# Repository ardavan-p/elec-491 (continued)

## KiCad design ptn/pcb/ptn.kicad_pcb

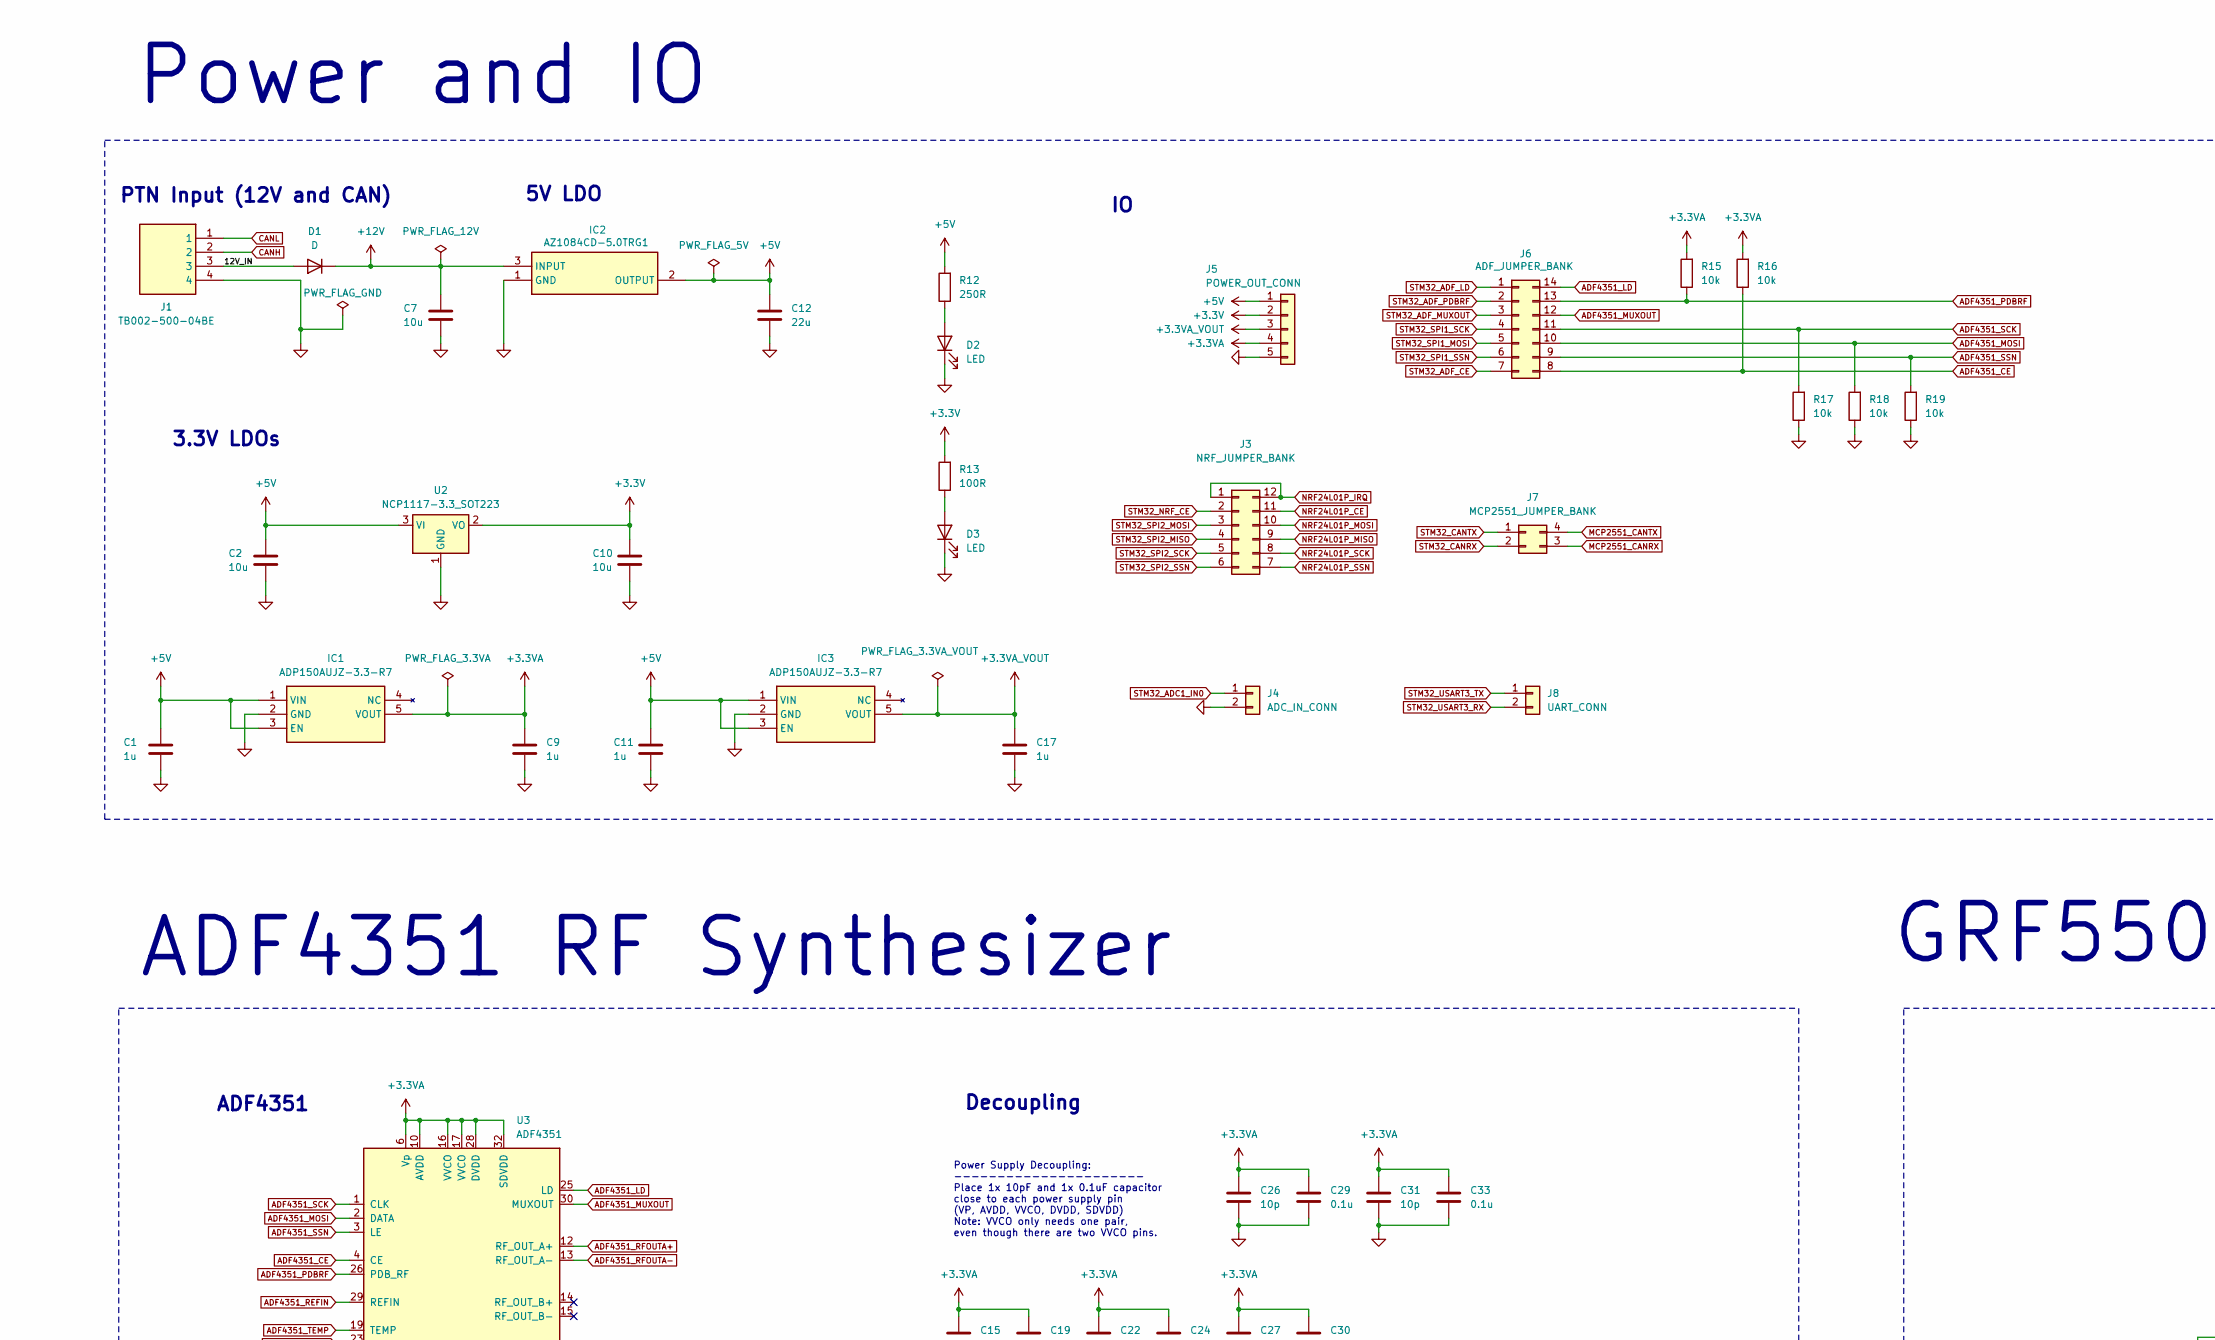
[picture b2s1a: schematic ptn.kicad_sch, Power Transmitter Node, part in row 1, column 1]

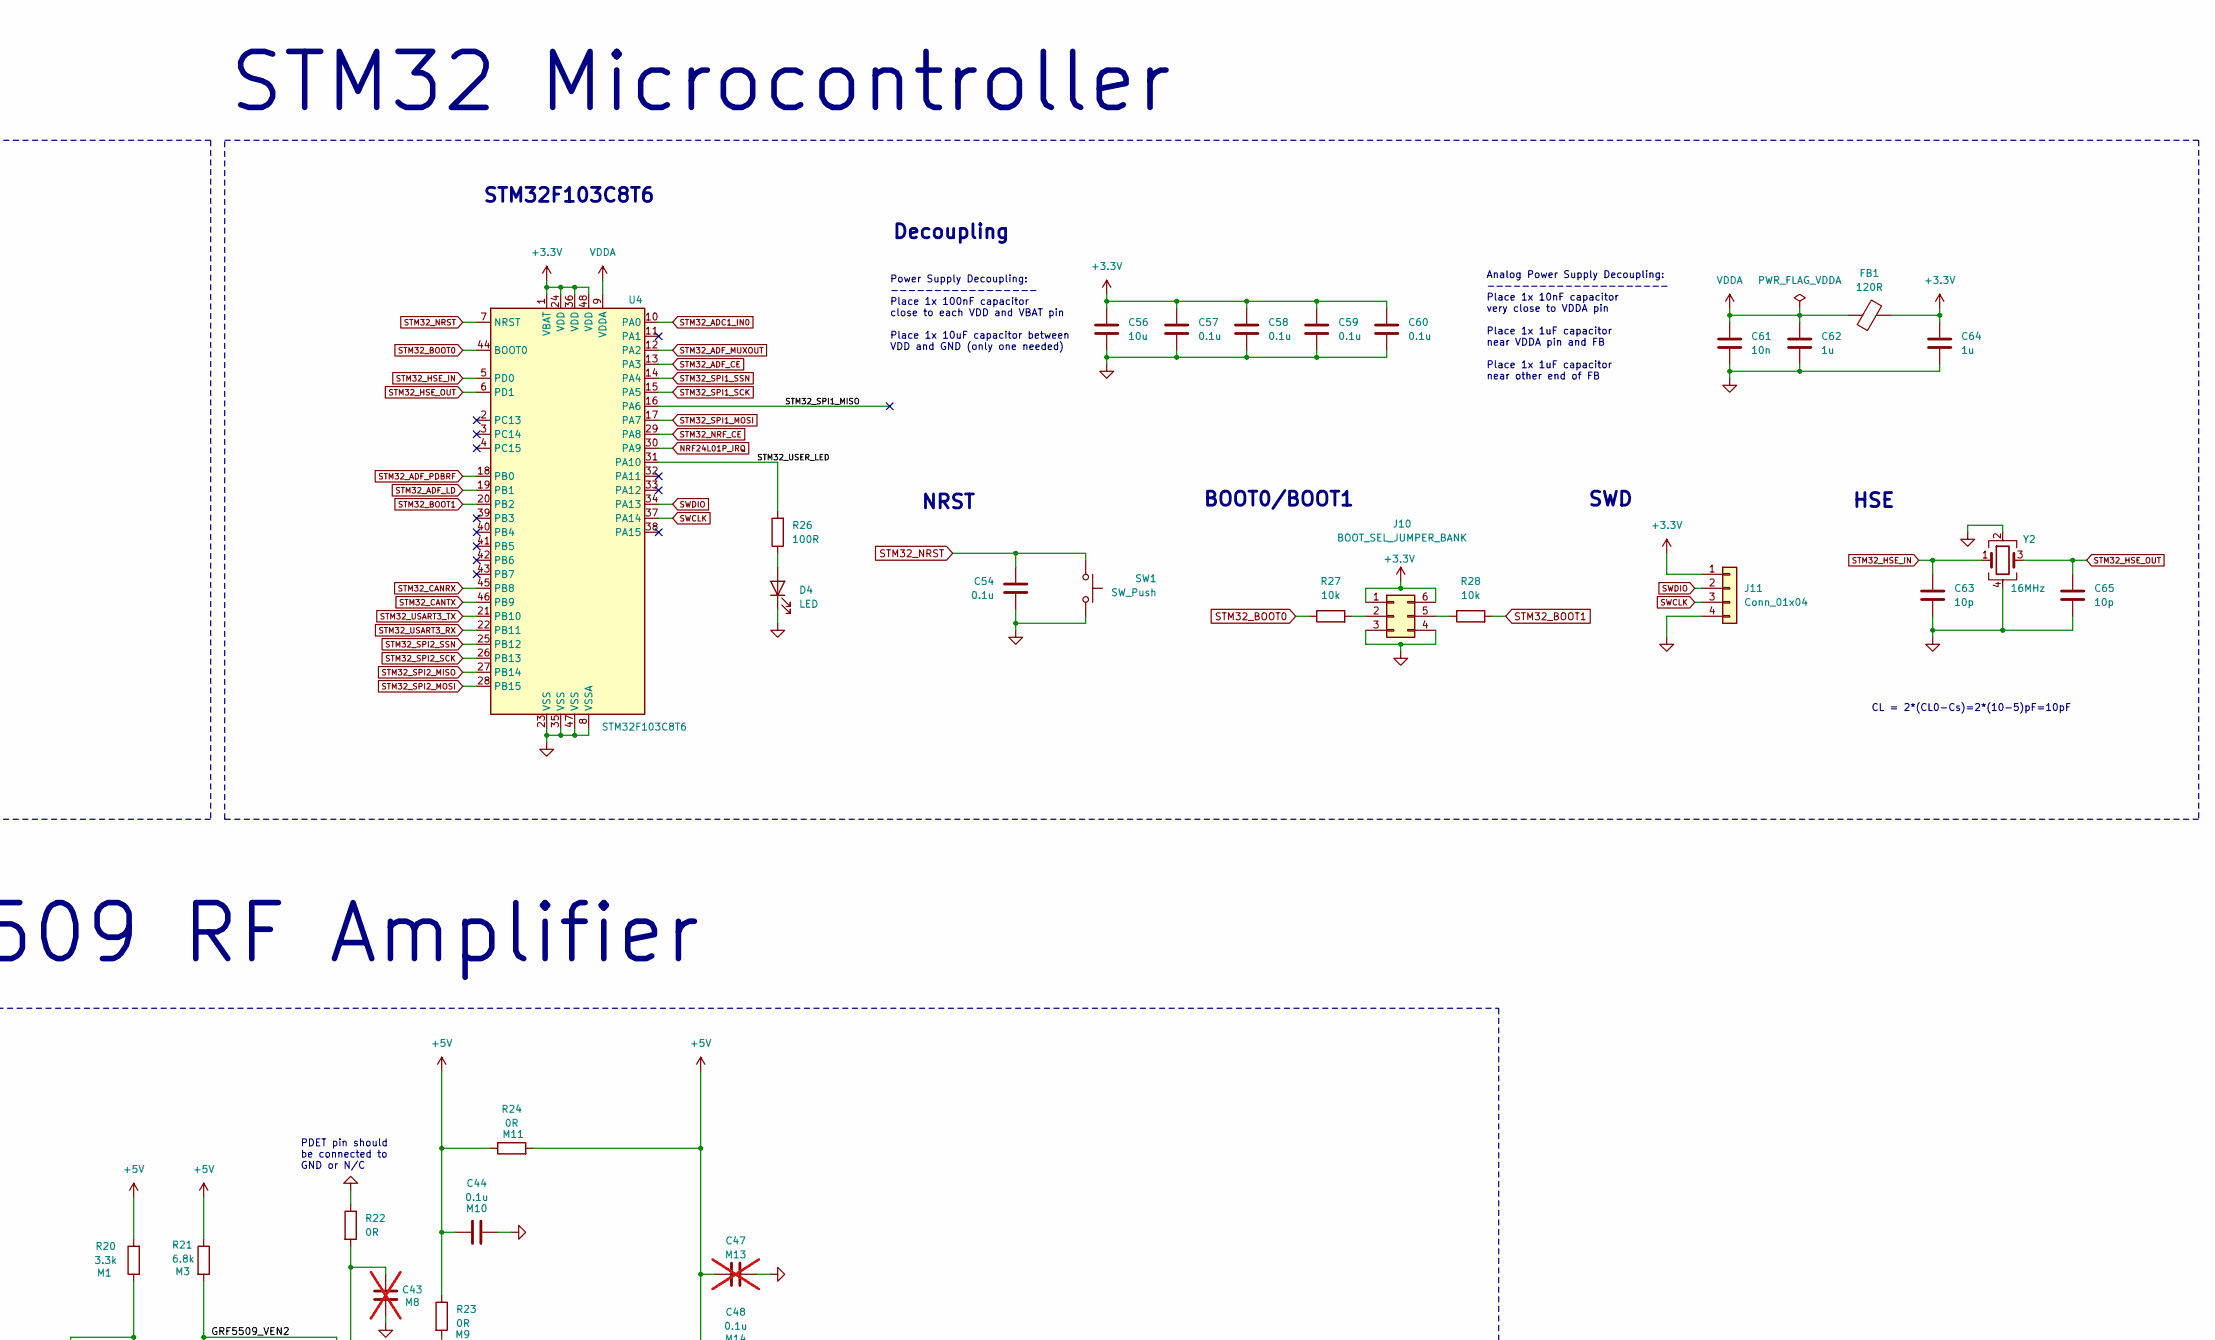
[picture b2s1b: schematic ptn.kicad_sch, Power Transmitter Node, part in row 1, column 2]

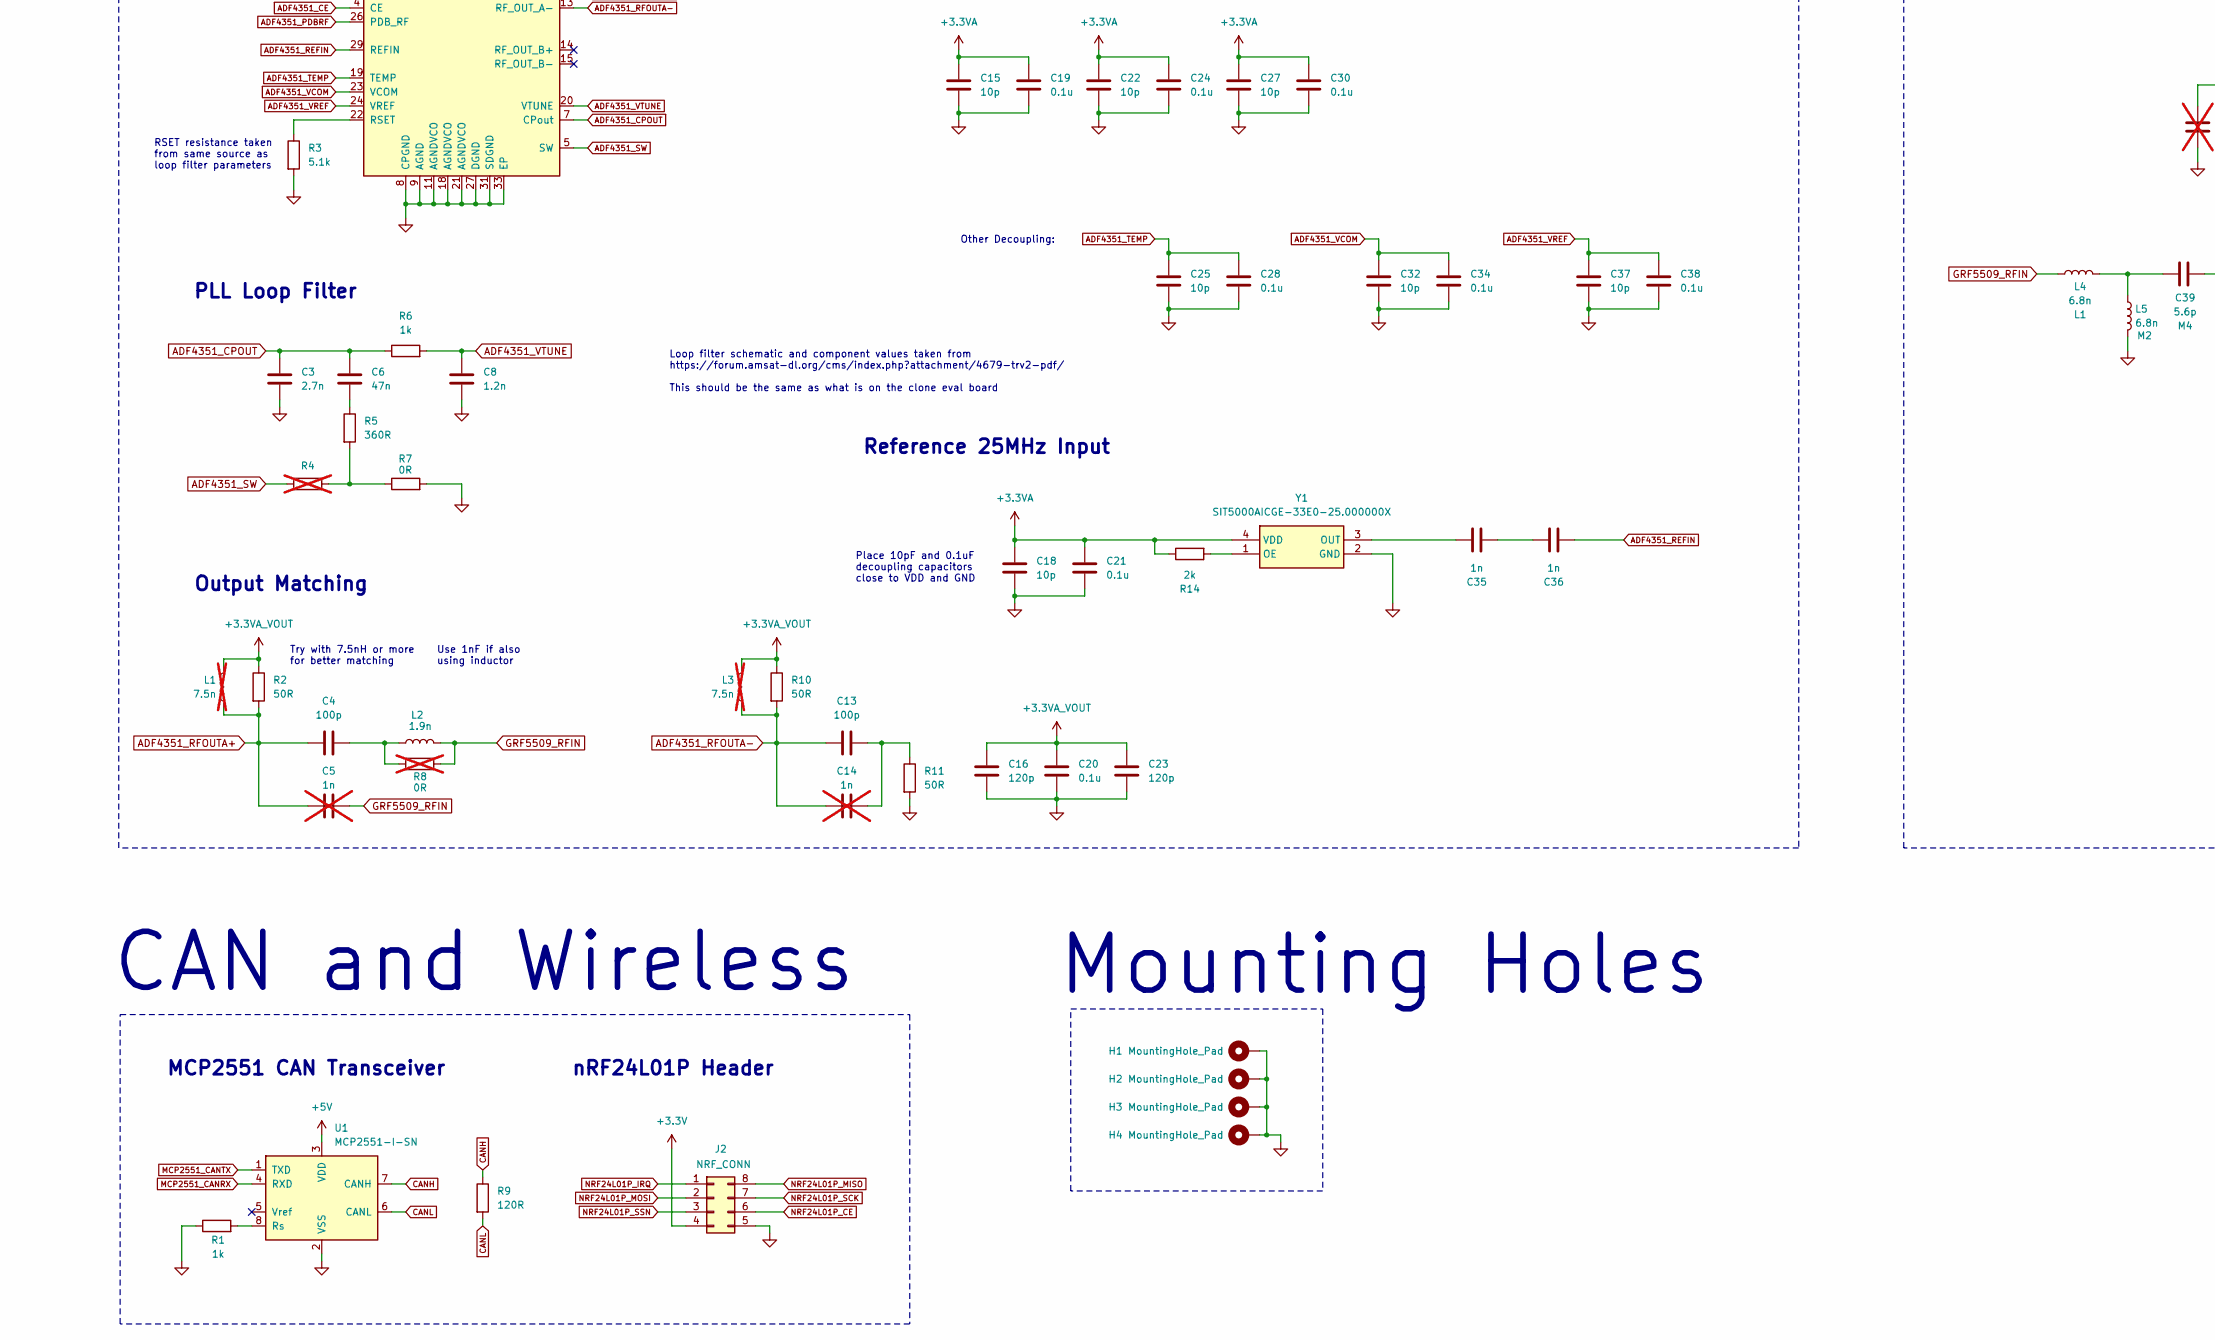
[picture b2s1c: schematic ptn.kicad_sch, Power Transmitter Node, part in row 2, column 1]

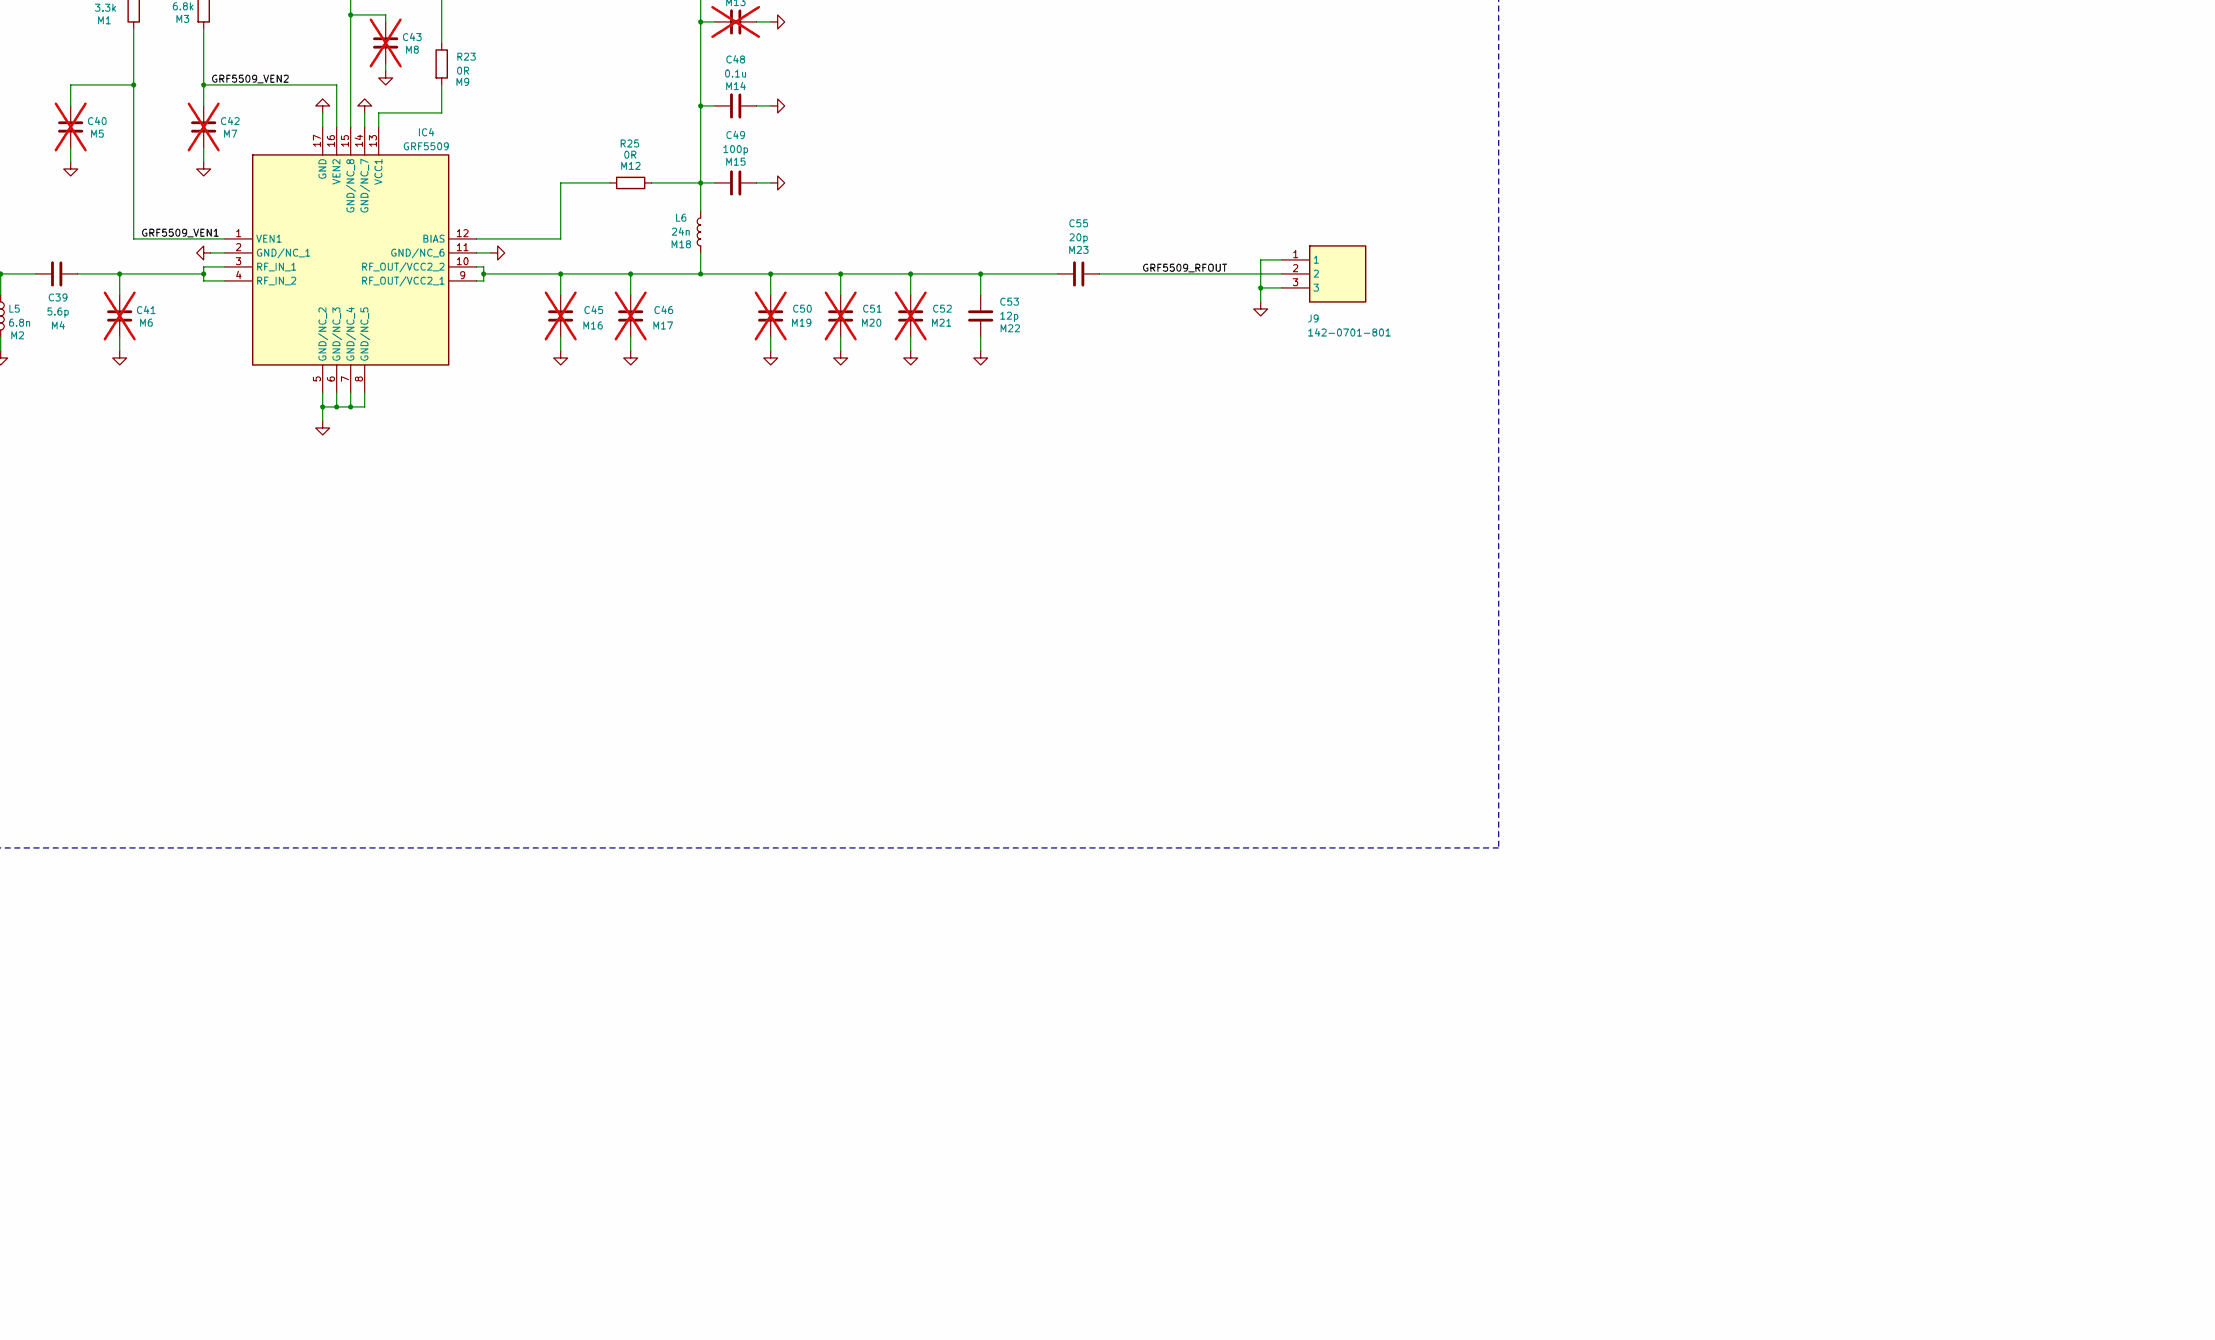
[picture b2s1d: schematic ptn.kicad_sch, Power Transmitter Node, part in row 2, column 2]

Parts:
C1, C9, C11, C17, C62, C64: 1u; C_0603_1608Metric; Manufacturer_Part_Number C0603C105K3PACTU; Mouser Part Number 80-C0603C105K3P
C2, C7, C10, C56: 10u; C_0805_2012Metric; Manufacturer_Part_Number GRM21BR61E106KA73K; Mouser Part Number 81-GRM21BR61E106KA3K
C3: 2.7n; C_0603_1608Metric; Manufacturer_Part_Number 06031C272JAT2A; Mouser Part Number 581-06031C272JAT2A
C4, C13, C49: 100p; C_0402_1005Metric; Manufacturer_Part_Number GRM1555C1H101FA01D; Mouser Part Number 81-GRM1555C1H101FA1D
C5, C14: 1n; C_0402_1005Metric; Manufacturer_Part_Number GRM1555C1H102FA01D; Mouser Part Number 81-GRM1555C1H102FA1D; not fitted
C6: 47n; C_0603_1608Metric; Manufacturer_Part_Number C0603C473J3RACTU; Mouser Part Number 80-C0603C473J3R
C8: 1.2n; C_0603_1608Metric; Manufacturer_Part_Number C0603C122J5RACTU; Mouser Part Number 80-C0603C122J5R
C12: 22u; C_0805_2012Metric; Manufacturer_Part_Number GRM21BR61E226ME44K; Mouser Part Number 81-GRM21BR61E226ME4K
C15, C18, C22, C25, C26, C27, C31, C32, C37, C63, C65: 10p; C_0402_1005Metric; Manufacturer_Part_Number GCM1555C1H100JA16J; Mouser Part Number 81-GCM1555C1H100JA6J
C16, C23: 120p; C_0402_1005Metric; Manufacturer_Part_Number GRM1555C1H121FA01D; Mouser Part Number 81-GRM1555C1H121FA1D
C19, C20, C21, C24, C28, C29, C30, C33, C34, C38, C44, C48, C54, C57, C58, C59, C60: 0.1u; C_0402_1005Metric; Manufacturer_Part_Number GRM155R71C104JA88J; Mouser Part Number 81-GRM155R71C104JA8J
C35, C36: 1n; C_0603_1608Metric; Manufacturer_Part_Number 06035A102JAT2A; Mouser Part Number 581-06035A102J
C39: 5.6p; C_0402_1005Metric; Manufacturer_Part_Number GJM1555C1H5R6WB01D; Mouser Part Number 81-GJM1555C1H5R6WB1D
C40, C41, C42, C43, C45, C46, C47, C50, C51, C52: C_0402_1005Metric; not fitted
C53: 12p; C_0402_1005Metric; Manufacturer_Part_Number GJM1555C1H120FB01D; Mouser Part Number 81-GJM1555C1H120FB1D
C55: 20p; C_0402_1005Metric; Manufacturer_Part_Number GJM1555C1H200FB01D; Mouser Part Number 81-GJM1555C1H200FB1D
C61: 10n; C_0402_1005Metric; Manufacturer_Part_Number C0402C103J8RACTU; Mouser Part Number 80-C0402C103J8RACTU
D1: D; RF302LAM2STR_DIODE; Manufacturer_Part_Number RF302LAM2STR; Mouser Part Number 755-RF302LAM2STR
D2, D3, D4: LED; LED_0603_1608Metric; Manufacturer_Part_Number 150060VS55040; Mouser Part Number 710-150060VS55040
FB1: 120R; L_0603_1608Metric; Manufacturer_Part_Number MFBM1V1608-121-R; Mouser Part Number 704-MFBM1V1608-121-R
H1, H2, H3, H4: MountingHole_Pad; MountingHole_4.3mm_M4_Pad
IC1, IC3: ADP150AUJZ-3.3-R7; SOT95P280X100-5N; Mouser Part Number 584-ADP150AUJZ-3.3R7
IC2: AZ1084CD-5.0TRG1; AZ1084CD50TRG1_LDO_5V; Mouser Part Number 621-AZ1084CD-5.0TRG1
IC4: GRF5509; QFN50P300X300X85-17N; Mouser Part Number 459-GRF5509
J1: TB002-500-04BE; TB00250004BE_SCREW_TERMINAL; Mouser Part Number 490-TB002-500-04BE
J2: NRF_CONN; PinSocket_2x04_P2.54mm_Vertical
J3: NRF_JUMPER_BANK; PinHeader_2x06_P2.54mm_Vertical
J4: ADC_IN_CONN; PinHeader_1x02_P2.54mm_Vertical
J5: POWER_OUT_CONN; PinHeader_1x05_P2.54mm_Vertical
J6: ADF_JUMPER_BANK; PinHeader_2x07_P2.54mm_Vertical
J7: MCP2551_JUMPER_BANK; PinHeader_2x02_P2.54mm_Vertical
J8: UART_CONN; PinHeader_1x02_P2.54mm_Vertical
J9: 142-0701-801; 142-0701-851; Mouser Part Number 530-142-0701-801
J10: BOOT_SEL_JUMPER_BANK; PinHeader_2x03_P2.54mm_Vertical
J11: Conn_01x04; PinHeader_1x04_P2.54mm_Vertical
L1, L3: 7.5n; L_0402_1005Metric; Manufacturer_Part_Number LQW15AN7N5G80D; Mouser Part Number 81-LQW15AN7N5G80D; not fitted
L2: 1.9n; L_0402_1005Metric; Manufacturer_Part_Number LQG15WZ1N9C02D; Mouser Part Number 81-LQG15WZ1N9C02D
L4, L5: 6.8n; L_0402_1005Metric; Manufacturer_Part_Number LQG15WH6N8G02D; Mouser Part Number 81-LQG15WH6N8G02D
L6: 24n; L_0603_1608Metric; Manufacturer_Part_Number LQW18AN24NG80D; Mouser Part Number 81-LQW18AN24NG80D
R1, R6: 1k; R_0603_1608Metric; Manufacturer_Part_Number RC0603FR-101KL; Mouser Part Number 603-RC0603FR-101KL
R2, R10, R11: 50R; R_0402_1005Metric; Manufacturer_Part_Number RC0402JR-0750RL; Mouser Part Number 603-RC0402JR-0750RL
R3: 5.1k; R_0603_1608Metric; Manufacturer_Part_Number CRCW06035K10FKEC; Mouser Part Number 71-CRCW06035K10FKEC
R4: R_0603_1608Metric; not fitted
R5: 360R; R_0603_1608Metric; Manufacturer_Part_Number RT0603DRE07360RL; Mouser Part Number 603-RT0603DRE07360RL
R7: 0R; R_0603_1608Metric; Manufacturer_Part_Number RCS06030000Z0EA; Mouser Part Number 71-RCS06030000Z0EA
R8: 0R; R_0402_1005Metric; Manufacturer_Part_Number RCS04020000Z0ED; Mouser Part Number 71-RCS04020000Z0ED; not fitted
R9: 120R; R_0603_1608Metric; Manufacturer_Part_Number RC0603FR-10120RL; Mouser Part Number 603-RC0603FR-10120RL
R12: 250R; R_0603_1608Metric; Manufacturer_Part_Number RT0603BRE07250RL; Mouser Part Number 603-RT0603BRE07250RL
R13, R26: 100R; R_0603_1608Metric; Manufacturer_Part_Number RT0603DRE07100RL; Mouser Part Number 603-RT0603DRE07100RL
R14: 2k; R_0603_1608Metric; Manufacturer_Part_Number RT0603FRE102KL; Mouser Part Number 603-RT0603FRE102KL
R15, R16, R17, R18, R19, R27, R28: 10k; R_0603_1608Metric; Manufacturer_Part_Number RT0603FRE1310KL; Mouser Part Number 603-RT0603FRE1310KL
R20: 3.3k; R_0402_1005Metric; Manufacturer_Part_Number ERJ-2GEJ332X; Mouser Part Number 667-ERJ-2GEJ332X
R21: 6.8k; R_0402_1005Metric; Manufacturer_Part_Number ERJ-2GEJ682X; Mouser Part Number 667-ERJ-2GEJ682X
R22, R23, R24, R25: 0R; R_0402_1005Metric; Manufacturer_Part_Number RCS04020000Z0ED; Mouser Part Number 71-RCS04020000Z0ED
SW1: SW_Push; SW_SPST_Omron_B3FS-100xP; Manufacturer_Part_Number B3FS-1002P; Mouser Part Number 653-B3FS-1002P
U1: MCP2551-I-SN; SOIC-8_3.9x4.9mm_P1.27mm; Manufacturer_Part_Number MCP2551-I/SN; Mouser Part Number 579-MCP2551-I/SN
U2: NCP1117-3.3_SOT223; SOT-223-3_TabPin2; Manufacturer_Part_Number NCP1117ST33T3G; Mouser Part Number 863-NCP1117ST33T3G
U3: ADF4351; LFCSP-32-1EP_5x5mm_P0.5mm_EP3.25x3.25mm; Manufacturer_Part_Number ADF4351BCPZ-RL7; Mouser Part Number 584-ADF4351BCPZ-R7
U4: STM32F103C8T6; LQFP-48_7x7mm_P0.5mm; Manufacturer_Part_Number STM32F103C8T6; Mouser Part Number 511-STM32F103C8T6
Y1: SIT5000AICGE-33E0-25.000000X; SIT5000AICGE33E025000000X; Mouser Part Number 788-5000AICGE3E0-25X
Y2: 16MHz; 16MHz_830108288709; Manufacturer_Part_Number 830108288709; Mouser Part Number 710-830108288709

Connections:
+3.3V: C10.1, C56.2, C57.2, C58.2, C59.2, C60.2, C64.2, FB1.2, J2.4, J5.2, J10.1, J10.6, J11.1, R13.2, U2.2 (VO), U4.1 (VBAT), U4.24 (VDD), U4.36 (VDD), U4.48 (VDD)
+3.3VA: C9.1, C15.1, C18.1, C19.1, C21.1, C22.1, C24.1, C26.1, C27.1, C29.1, C30.1, C31.1, C33.1, IC1.5 (VOUT), J5.4, R14.1, R15.2, R16.2, U3.6 (Vp), U3.10 (AVDD), U3.16 (VVCO), U3.17 (VVCO), U3.28 (DVDD), U3.32 (SDVDD), Y1.4 (VDD)
+3.3VA_VOUT: C16.1, C17.1, C20.1, C23.1, IC3.5 (VOUT), J5.3, L1.1, L3.1, R2.1, R10.1
+5V: C1.1, C2.1, C11.1, C12.1, C44.2, C47.1, C48.1, C49.1, IC1.1 (VIN), IC1.3 (EN), IC2.2 (OUTPUT), IC3.1 (VIN), IC3.3 (EN), J5.1, L6.2, R12.2, R20.2, R21.1, R23.1, R24.1, R24.2, R25.1, U1.3 (VDD), U2.3 (VI)
+12V: C7.1, D1.1 (K), IC2.3 (INPUT)
/12V_IN: D1.2 (A), J1.3
/GRF5509_RFOUT: C55.2, J9.2
/GRF5509_VEN1: C40.1, IC4.1 (VEN1), R20.1
/GRF5509_VEN2: C42.1, IC4.16 (VEN2), R21.2
/STM32_SPI1_MISO: U4.16 (PA6)
/STM32_USER_LED: R26.2, U4.31 (PA10)
ADF4351_CE: J6.8, R16.1, U3.4 (CE)
ADF4351_CPOUT: C3.1, C6.1, R6.1, U3.7 (CPout)
ADF4351_LD: J6.14, U3.25 (LD)
ADF4351_MOSI: J6.10, R18.2, U3.2 (DATA)
ADF4351_MUXOUT: J6.12, U3.30 (MUXOUT)
ADF4351_PDBRF: J6.13, R15.1, U3.26 (PDB_RF)
ADF4351_REFIN: C36.2, U3.29 (REFIN)
ADF4351_RFOUTA+: C4.1, C5.1, L1.2, R2.2, U3.12 (RF_OUT_A+)
ADF4351_RFOUTA-: C13.1, C14.1, L3.2, R10.2, U3.13 (RF_OUT_A-)
ADF4351_SCK: J6.11, R17.2, U3.1 (CLK)
ADF4351_SSN: J6.9, R19.2, U3.3 (LE)
ADF4351_SW: R4.1, U3.5 (SW)
ADF4351_TEMP: C25.1, C28.1, U3.19 (TEMP)
ADF4351_VCOM: C32.1, C34.1, U3.23 (VCOM)
ADF4351_VREF: C37.1, C38.1, U3.24 (VREF)
ADF4351_VTUNE: C8.1, R6.2, U3.20 (VTUNE)
CANH: J1.2, R9.1, U1.7 (CANH)
CANL: J1.1, R9.2, U1.6 (CANL)
GND: C1.2, C2.2, C3.2, C7.2, C8.2, C9.2, C10.2, C11.2, C12.2, C15.2, C16.2, C17.2, C18.2, C19.2, C20.2, C21.2, C22.2, C23.2, C24.2, C25.2, C26.2, C27.2, C28.2, C29.2, C30.2, C31.2, C32.2, C33.2, C34.2, C37.2, C38.2, C40.2, C41.2, C42.2, C43.2, C44.1, C45.1, C46.1, C47.2, C48.2, C49.2, C50.1, C51.1, C52.1, C53.1, C54.1, C56.1, C57.1, C58.1, C59.1, C60.1, C61.1, C62.1, C63.1, C64.1, C65.1, D2.1 (K), D3.1 (K), D4.1 (K), H1.1, H2.1, H3.1, H4.1, IC1.2 (GND), IC2.1 (GND), IC3.2 (GND), IC4.2 (GND/NC_1), IC4.5 (GND/NC_2), IC4.6 (GND/NC_3), IC4.7 (GND/NC_4), IC4.8 (GND/NC_5), IC4.11 (GND/NC_6), IC4.14 (GND/NC_7), IC4.17 (GND), J1.4, J2.5, J4.2, J5.5, J9.1, J9.3, J10.3, J10.4, J11.4, L5.2, R1.1, R3.2, R7.2, R11.2, R17.1, R18.1, R19.1, R22.1, SW1.1, U1.2 (VSS), U2.1 (GND), U3.8 (CPGND), U3.9 (AGND), U3.11 (AGNDVCO), U3.18 (AGNDVCO), U3.21 (AGNDVCO), U3.27 (DGND), U3.31 (SDGND), U3.33 (EP), U4.8 (VSSA), U4.23 (VSS), U4.35 (VSS), U4.47 (VSS), Y1.2 (GND), Y2.2, Y2.4
GRF5509_RFIN: C5.2, L2.2, L4.1, R8.1
MCP2551_CANRX: J7.3, U1.4 (RXD)
MCP2551_CANTX: J7.4, U1.1 (TXD)
NRF24L01P_CE: J2.6, J3.11
NRF24L01P_IRQ: J2.1, J3.1, J3.12, U4.30 (PA9)
NRF24L01P_MISO: J2.8, J3.9
NRF24L01P_MOSI: J2.2, J3.10
NRF24L01P_SCK: J2.7, J3.8
NRF24L01P_SSN: J2.3, J3.7
unnamed: C4.2, L2.1, R8.2
unnamed: C6.2, R5.1
unnamed: C13.2, C14.2, R11.1
unnamed: C35.2, C36.1
unnamed: C39.1, L4.2, L5.1
unnamed: D2.2 (A), R12.1
unnamed: D3.2 (A), R13.1
unnamed: D4.2 (A), R26.1
unnamed: IC4.12 (BIAS), R25.2
unnamed: C43.1, IC4.15 (GND/NC_8), R22.2
unnamed: C39.2, C41.1, IC4.3 (RF_IN_1), IC4.4 (RF_IN_2)
unnamed: C45.2, C46.2, C50.2, C51.2, C52.2, C53.2, C55.1, IC4.9 (RF_OUT/VCC2_1), IC4.10 (RF_OUT/VCC2_2), L6.1
unnamed: IC4.13 (VCC1), R23.2
unnamed: J10.2, R27.2
unnamed: J10.5, R28.1
unnamed: R4.2, R5.2, R7.1
unnamed: R1.2, U1.8 (Rs)
unnamed: R3.1, U3.22 (RSET)
unnamed: R14.2, Y1.1 (OE)
unnamed: C35.1, Y1.3 (OUT)
STM32_ADC1_IN0: J4.1, U4.10 (PA0)
STM32_ADF_CE: J6.7, U4.13 (PA3)
STM32_ADF_LD: J6.1, U4.19 (PB1)
STM32_ADF_MUXOUT: J6.3, U4.12 (PA2)
STM32_ADF_PDBRF: J6.2, U4.18 (PB0)
STM32_BOOT0: R27.1, U4.44 (BOOT0)
STM32_BOOT1: R28.2, U4.20 (PB2)
STM32_CANRX: J7.2, U4.45 (PB8)
STM32_CANTX: J7.1, U4.46 (PB9)
STM32_HSE_IN: C63.2, U4.5 (PD0), Y2.1
STM32_HSE_OUT: C65.2, U4.6 (PD1), Y2.3
STM32_NRF_CE: J3.2, U4.29 (PA8)
STM32_NRST: C54.2, SW1.2, U4.7 (NRST)
STM32_SPI1_MOSI: J6.5, U4.17 (PA7)
STM32_SPI1_SCK: J6.4, U4.15 (PA5)
STM32_SPI1_SSN: J6.6, U4.14 (PA4)
STM32_SPI2_MISO: J3.4, U4.27 (PB14)
STM32_SPI2_MOSI: J3.3, U4.28 (PB15)
STM32_SPI2_SCK: J3.5, U4.26 (PB13)
STM32_SPI2_SSN: J3.6, U4.25 (PB12)
STM32_USART3_RX: J8.2, U4.22 (PB11)
STM32_USART3_TX: J8.1, U4.21 (PB10)
SWCLK: J11.3, U4.37 (PA14)
SWDIO: J11.2, U4.34 (PA13)
VDDA: C61.2, C62.2, FB1.1, U4.9 (VDDA)

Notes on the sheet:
BOOT0/BOOT1
HSE
Mounting Holes
PDET pin should be connected to GND or N/C
NRST
ADF4351
Decoupling
CAN and Wireless
Power and IO
Other Decoupling:
ADF4351 RF Synthesizer
MCP2551 CAN Transceiver
CL = 2*(CL0-Cs)=2*(10-5)pF=10pF
Try with 7.5nH or more for better matching
Power Supply Decoupling: ----------------- Place 1x 100nF capacitor close to each VDD and VBAT pin Place 1x 10uF capacitor between VDD and GND (only one needed)
GRF5509 RF Amplifier
3.3V LDOs
PTN Input (12V and CAN)
Analog Power Supply Decoupling: --------------------- Place 1x 10nF capacitor very close to VDDA pin Place 1x 1uF capacitor near VDDA pin and FB Place 1x 1uF capacitor near other end of FB
Place 10pF and 0.1uF decoupling capacitors close to VDD and GND
Use 1nF if also using inductor
PLL Loop Filter
RSET resistance taken from same source as loop filter parameters
Power Supply Decoupling: ---------------------- Place 1x 10pF and 1x 0.1uF capacitor close to each power supply pin (VP, AVDD, VVCO, DVDD, SDVDD) Note: VVCO only needs one pair, even though there are two VVCO pins.
STM32 Microcontroller
nRF24L01P Header
Reference 25MHz Input
Output Matching
5V LDO
Loop filter schematic and component values taken from https://forum.amsat-dl.org/cms/index.php?attachment/4679-trv2-pdf/ This should be the same as what is on the clone eval board
STM32F103C8T6
SWD
